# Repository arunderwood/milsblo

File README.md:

# milsblo

**milsblo** is a portmanteau of **[MILSBO](https://www.ikea.com/us/en/p/milsbo-glass-door-cabinet-anthracite-30396448/)** — IKEA's popular glass-door cabinet — and ***blow***, for the fan-control feature at the heart of the board.

> An experiment in vibe-coded circuit design by someone without much electronics experience.

## Background

Hobbyists convert MILSBO cabinets into [miniature indoor greenhouses](https://daught.me/blog/2024/ikea-milsbo-greenhouse/) using grow lights, humidifiers, and fans. Circulation fans are critical: airflow strengthens stems and prevents the mold that thrives in warm, stagnant, humid air.

**milsblo** is the electronics backbone for that setup.

## What it does

A 12V DC supply on a 5.5 × 2.1mm barrel jack powers both fans and the microcontroller from one cord. The board backpacks onto an ESP32-S3-DevKitC-1 via female pin headers.

```
12V DC supply (centre positive, 1.5A+)
    │
    ▼
Barrel jack → AO3407A → 12V rail ──→ Fan headers × 2 (always-on 12V)
                                └──→ AP63205 buck → 5V → ESP32-S3-DevKitC-1
                                                         │
                                                         ├── 25kHz PWM → Fan 1 & 2 speed control
                                                         ├── Tach input ← Fan RPM feedback
                                                         └── I2C → BME280 temp/humidity sensor
```

- **Power:** 12V barrel jack with reverse-polarity protection (AO3407A); stepped to 5V by AP63205 buck converter
- **Fan control:** 25kHz PWM on GPIO 4/5 (silent, full-range speed), tach feedback on GPIO 6/7
- **Sensor:** BME280 via JST-SH 4-pin (Qwiic/STEMMA QT compatible) on I2C GPIO 8/9
- **Firmware:** ESPHome (`firmware/milsblo.yaml`) — integrates with Home Assistant

## Project status

| Phase | Status |
|-------|--------|
| Phase 1: Component definitions | ✅ Complete |
| Phase 2: KiCad schematic | ✅ Complete |
| Phase 3: SPICE simulations | ✅ Complete |
| Phase 4: Firmware + test guide | ✅ Complete |
| Phase 5: PCB layout (KiCad) | ✅ Complete |
| Phase 6: Manufacturing export | ✅ Complete (`tools/export_fab.sh`) |

## Design

Designed in [KiCad](https://www.kicad.org/). The project lives in `elec/kicad/`, and `tools/check_design.py` checks it against the part datasheets.

**For full architecture decisions and build instructions, see [CLAUDE.md](CLAUDE.md).**

## Toolchain

```bash
python3 tools/check_design.py       # ERC, DRC, parity, connectivity, datasheet and layout rules
tools/export_fab.sh                 # Gerber zip, BOM and pick-and-place in elec/build/fab
ngspice -b simulation/power_chain.cir
esphome run firmware/milsblo.yaml
```

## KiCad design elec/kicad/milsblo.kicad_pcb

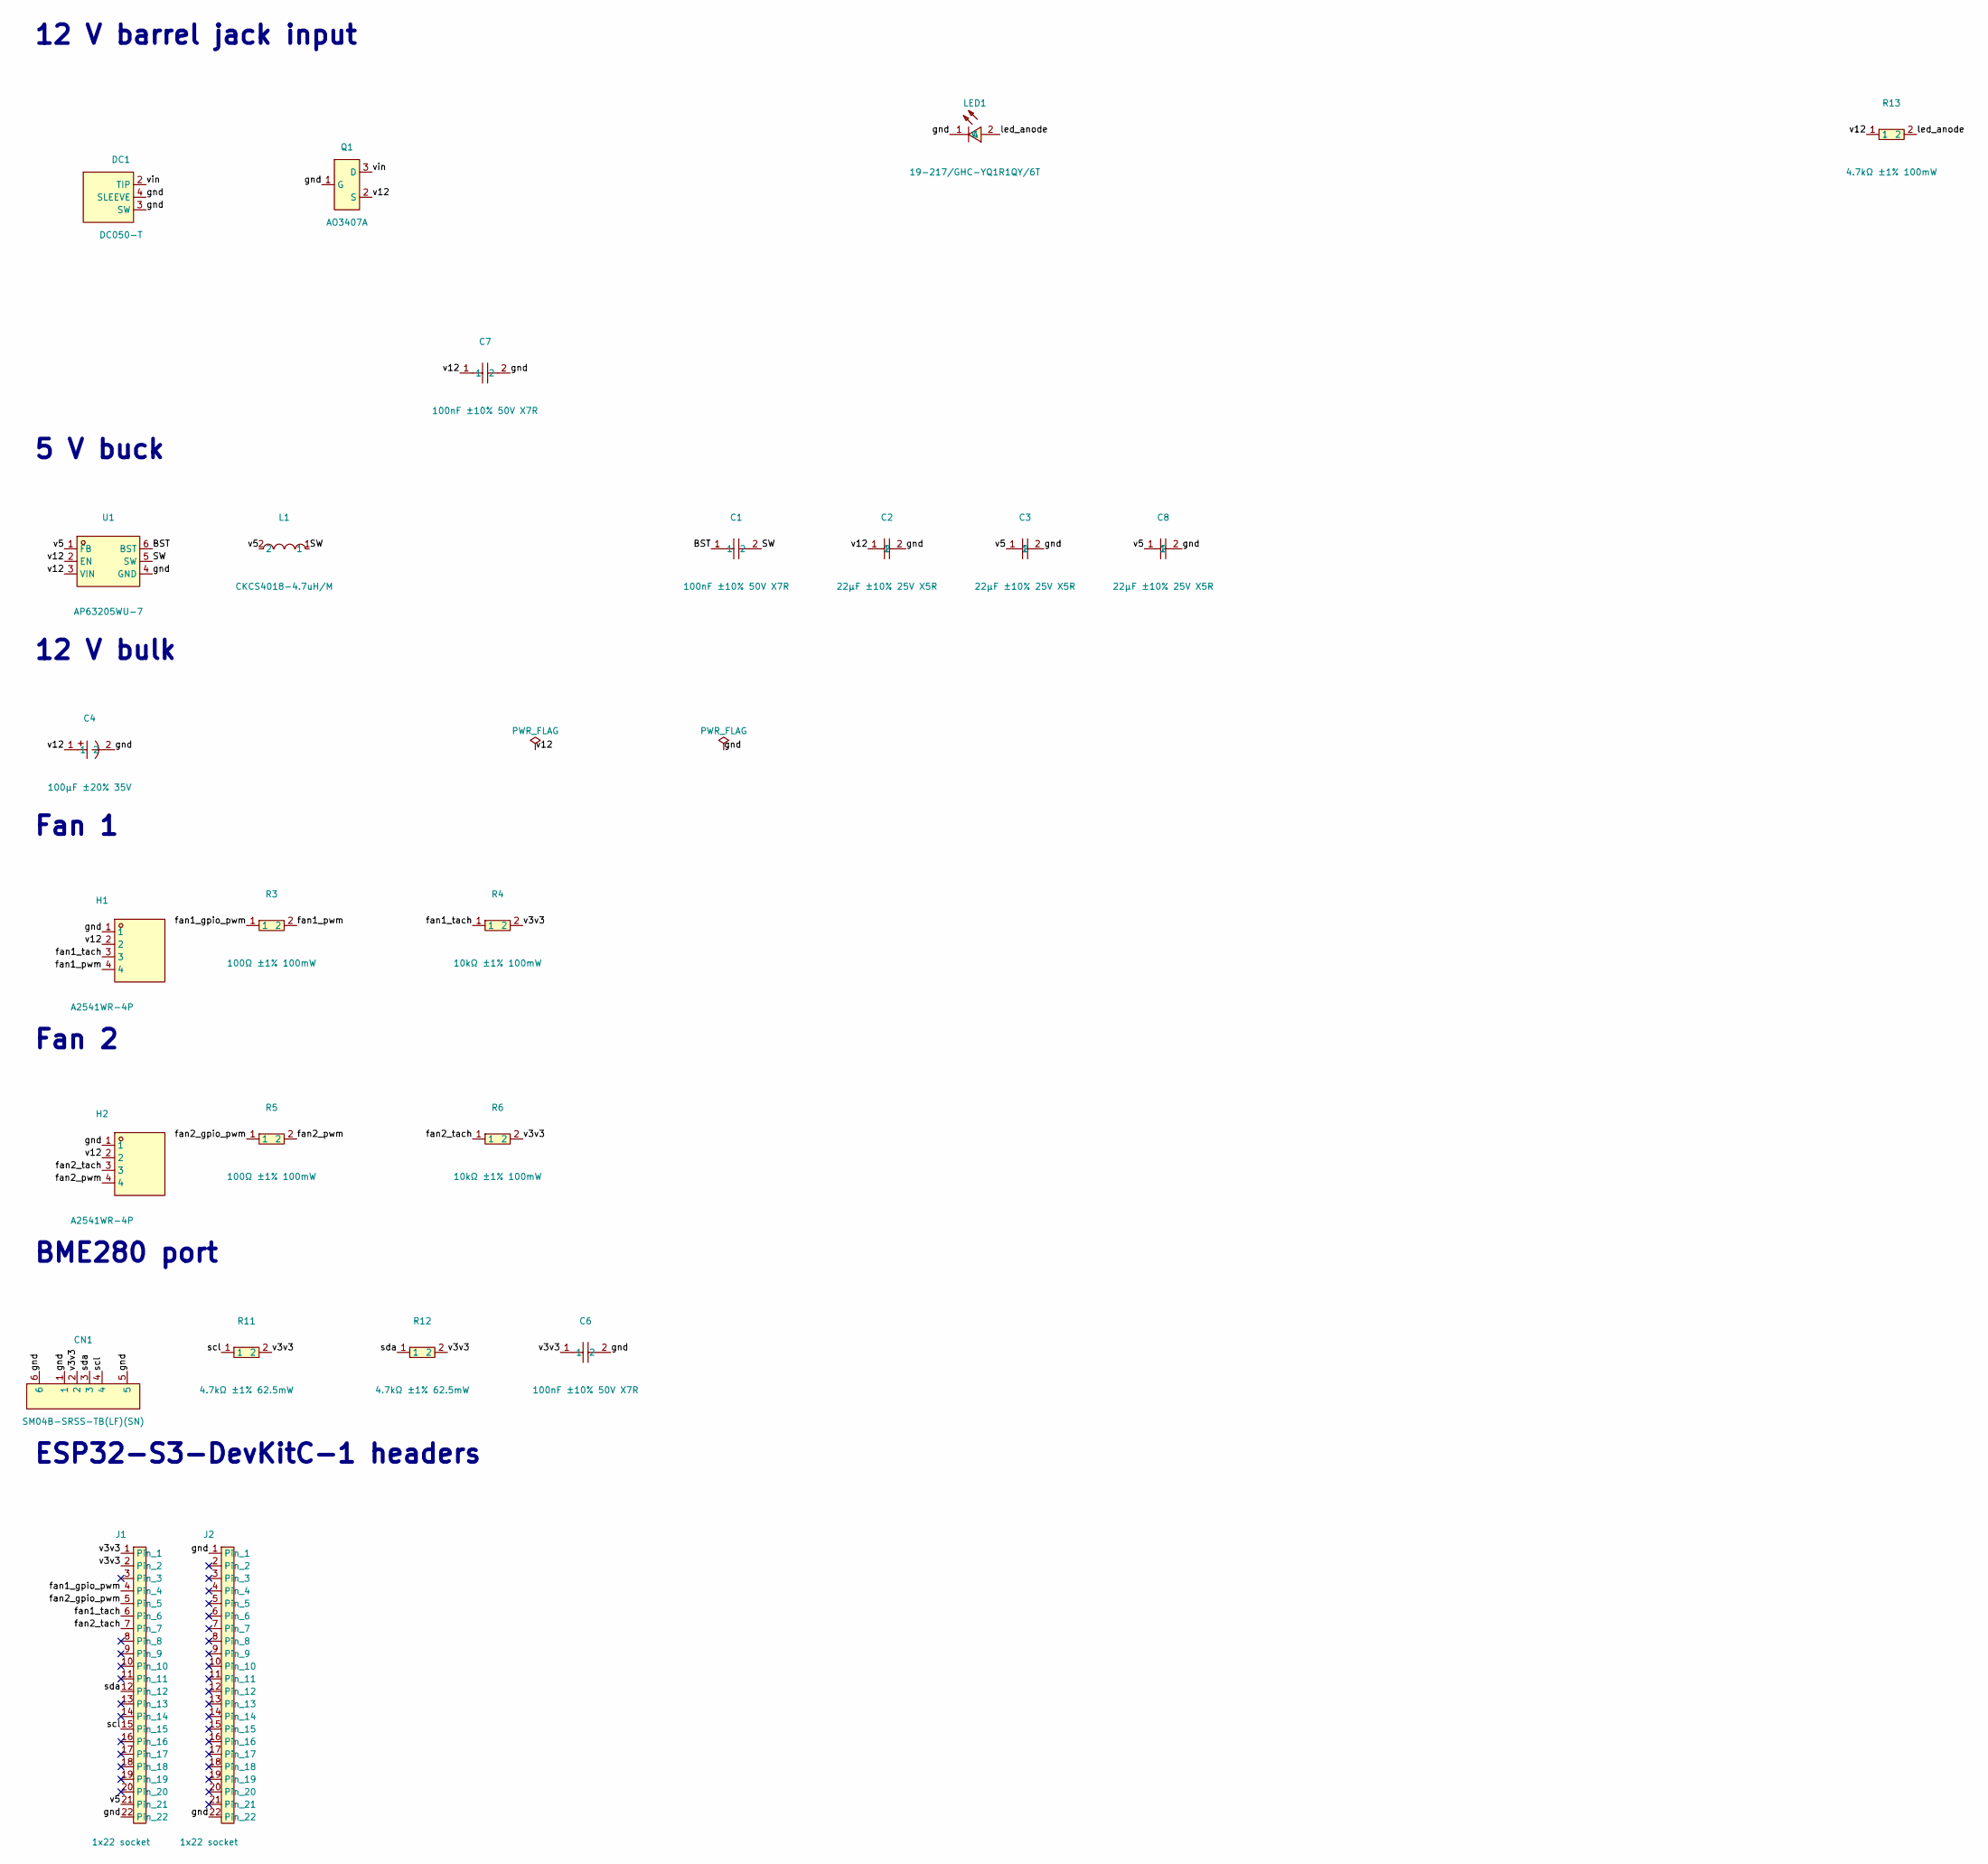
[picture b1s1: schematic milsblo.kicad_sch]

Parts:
C1, C6, C7: 100nF ±10% 50V X7R; C0603; Partnumber CC0603KRX7R9BB104; LCSC Part C14663
C2, C3, C8: 22µF ±10% 25V X5R; C1206; Partnumber CL31A226KAHNNNE; LCSC Part C12891
C4: 100µF ±20% 35V; CAP-SMD_BD6.3-L6.6-W6.6-FD; Partnumber RVT100UF35V167RV0082; LCSC Part C5138965
CN1: SM04B-SRSS-TB(LF)(SN); CONN-SMD_4P-P1.00_SM04B-SRSS-TB-LF-SN; Partnumber SM04B-SRSS-TB(LF)(SN); LCSC Part C160404
DC1: DC050-T; DC-SMD_DC050-T; Partnumber DC050-T; LCSC Part C431534
H1, H2: A2541WR-4P; HDR-TH_4P-P2.54-H-M-W10.3; Partnumber A2541WR-4P; LCSC Part C225490
J1, J2: 1x22 socket; PinSocket_1x22_P2.54mm_Vertical; Partnumber HC-PM254-8.5H-1x22PZ; LCSC Part C41376161
L1: CKCS4018-4.7uH/M; IND-SMD_L4.0-W4.0_SWPA4018S; Partnumber CKCS4018-4.7uH/M; LCSC Part C354574
LED1: 19-217/GHC-YQ1R1QY/6T; LED0603-RD; Partnumber 19-217/GHC-YQ1R1QY/6T; LCSC Part C2986032
Q1: AO3407A; SOT-23-3_L2.9-W1.6-P1.90-LS2.8-BR; Partnumber AO3407A; LCSC Part C15155
R3, R5: 100Ω ±1% 100mW; R0603; Partnumber 0603WAF1000T5E; LCSC Part C22775
R4, R6: 10kΩ ±1% 100mW; R0603; Partnumber 0603WAF1002T5E; LCSC Part C25804
R11, R12: 4.7kΩ ±1% 62.5mW; R0402; Partnumber 0402WGF4701TCE; LCSC Part C25900
R13: 4.7kΩ ±1% 100mW; R0603; Partnumber 0603WAF4701T5E; LCSC Part C23162
U1: AP63205WU-7; TSOT-23-6_L2.9-W1.6-P0.95-LS2.8-BL; Partnumber AP63205WU-7; LCSC Part C2071056

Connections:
/BST: C1.1, U1.6 (BST)
/SW: C1.2, L1.1, U1.5 (SW)
/fan1_gpio_pwm: J1.4, R3.1
/fan1_pwm: H1.4, R3.2
/fan1_tach: H1.3, J1.6, R4.1
/fan2_gpio_pwm: J1.5, R5.1
/fan2_pwm: H2.4, R5.2
/fan2_tach: H2.3, J1.7, R6.1
/gnd: C2.2, C3.2, C4.2, C6.2, C7.2, C8.2, CN1.1, CN1.5, CN1.6, DC1.3 (SW), DC1.4 (SLEEVE), H1.1, H2.1, J1.22, J2.1, J2.22, LED1.1 (C), Q1.1 (G), U1.4 (GND)
/led_anode: LED1.2 (A), R13.2
/scl: CN1.4, J1.15, R11.1
/sda: CN1.3, J1.12, R12.1
/v3v3: C6.1, CN1.2, J1.1, J1.2, R4.2, R6.2, R11.2, R12.2
/v5: C3.1, C8.1, J1.21, L1.2, U1.1 (FB)
/v12: C2.1, C4.1, C7.1, H1.2, H2.2, Q1.2 (S), R13.1, U1.2 (EN), U1.3 (VIN)
/vin: DC1.2 (TIP), Q1.3 (D)

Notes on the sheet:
12 V bulk
12 V barrel jack input
5 V buck
BME280 port
Fan 1
ESP32-S3-DevKitC-1 headers
Fan 2

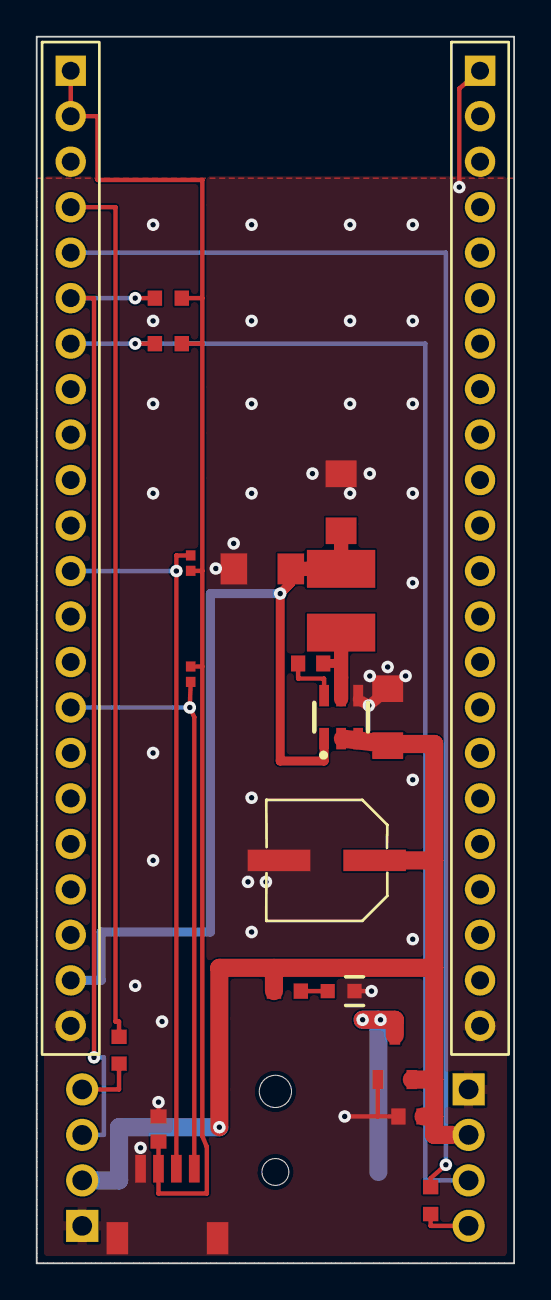
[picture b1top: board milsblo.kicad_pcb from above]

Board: 2 copper layers, 26.7 x 68.5 mm, 24 parts (1 on the bottom side), 16 nets.

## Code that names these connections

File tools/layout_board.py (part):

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    path("/gnd", F, SIG_W, (19.05, 58.24), (19.05, 60.3)),
    path("/gnd", F, SIG_W, (20.2, 60.3), (17.2, 60.3)),
    # 3.3 V from the top of J1 to the pullups and the sensor connector.
    path("/v3v3", F, SIG_W, (J1_X, pin_y(1)), (J1_X, pin_y(2))),
    path("/v3v3", F, SIG_W, (J1_X, pin_y(2)), (3.4, pin_y(2)), (3.4, 8.0), (9.25, 8.0), (9.25, 61.4), (9.5, 62.0), (9.5, 64.6), (6.8, 64.6), (6.8, 63.5)),
    path("/v3v3", F, SIG_W, (9.25, pin_y(6)), (8.1, pin_y(6))),
    path("/v3v3", F, SIG_W, (9.25, pin_y(7)), (8.1, pin_y(7))),
    path("/v3v3", F, SIG_W, (9.25, 29.83), (8.6, 29.83)),
    path("/v3v3", F, SIG_W, (9.25, 35.17), (8.6, 35.17)),
    path("/v3v3", F, SIG_W, (6.8, 61.7), (6.8, 62.8)),
    path("/gnd", F, SIG_W, (6.8, 60.3), (6.8, 59.5)),
    # Fan 1
    path("/fan1_gpio_pwm", F, SIG_W, (J1_X, pin_y(4)), (4.4, pin_y(4)), (4.4, 55.0), (4.6, 55.0), (4.6, 55.85)),
    path("/fan1_pwm", F, SIG_W, (4.6, 57.35), (4.6, 58.79), (3.44, 58.79)),
    path("/fan1_tach", F, SIG_W, (J1_X, pin_y(6)), (3.2, pin_y(6)), (3.2, 57.0)),
    path("/fan1_tach", B, SIG_W, (3.2, 57.0), (3.75, 57.0), (3.75, 61.33), (3.2, 61.33)),
    path("/fan1_tach", B, SIG_W, (J1_X, pin_y(6)), (5.5, pin_y(6))),
    path("/fan1_tach", F, SIG_W, (5.5, pin_y(6)), (6.6, pin_y(6))),
    # Fan 2 crosses on the bottom layer, under the fan 1 and I2C verticals.
    path("/fan2_gpio_pwm", B, SIG_W, (J1_X, pin_y(5)), (22.85, pin_y(5)), (22.85, 63.0)),
    path("/fan2_gpio_pwm", F, SIG_W, (22.85, 63.0), (22.0, 63.75), (22.0, 64.25)),
    path("/fan2_pwm", F, SIG_W, (22.0, 65.75), (22.0, 66.41), (23.22, 66.41)),
    path("/fan2_tach", B, SIG_W, (J1_X, pin_y(7)), (21.7, pin_y(7)), (21.7, 63.87), (23.22, 63.87)),
    path("/fan2_tach", F, SIG_W, (5.5, pin_y(7)), (6.6, pin_y(7))),
    # I2C
    path("/sda", B, SIG_W, (J1_X, pin_y(12)), (7.8, pin_y(12))),
    path("/sda", F, SIG_W, (7.8, pin_y(12)), (7.8, 62.45)),
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    ("/vin", 18.2, 54.9),
    ("/vin", 19.2, 54.9),
    ("/fan1_tach", 3.2, 57.0),
    ("/fan1_tach", 5.5, pin_y(6)),
    ("/fan2_tach", 5.5, pin_y(7)),
    ("/fan2_gpio_pwm", 22.85, 63.0),
    ("/sda", 7.8, pin_y(12)),
    ("/scl", 8.55, pin_y(15)),
    # Ground: regulator return, capacitor returns and pad tie-downs.
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
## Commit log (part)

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2026-02-17 Fix CLAUDE.md hardware design errors and add missing caveats
    Correct fan header pinout for low-side N-MOSFET switching topology,
    add tach signal validity caveat, fix DevKit board dimensions, pin
    Atopile to stable v0.12.x, add AP63205 thermal via requirement,
    USB-C connector verification note, BME280 self-heating offset,
    CH224K PD version info, and 3.3V current budget clarification.
2026-02-17 Initialize uv project and Atopile structure
    - Set up uv project with Python 3.13 (atopile 0.12.5 requirement)
    - Add atopile>=0.12,<0.13 dependency (pinned to stable release)
    - Create elec/ directory with modular src/ structure:
    - src/milsblo.ato (top-level board module)
    - src/power/ (usb_pd.ato, buck_5v.ato)
    - src/fan/ (fan_driver.ato)
2026-02-17 Replace PlatformIO firmware with ESPHome configuration
    Change Phase 7 from writing C++ firmware to crafting ESPHome YAML:
    - Complete milsblo.yaml with fan control, BME280 sensor, and tach reading
    - LEDC PWM at 25kHz on GPIO 4/5 for silent fan operation
    - Pulse counter for tach on GPIO 6/7 with RPM calculation
    - BME280 I2C with -1°C offset for self-heating compensation
    - Native Home Assistant integration via API
2026-02-18 Update CLAUDE.md for 4-pin PWM fan topology
    Remove AO3400A MOSFET and SS14 flyback diode (4-pin fans have internal
    controllers). Update fan headers from 3-pin to 4-pin throughout. Fix
    AP63205WU-7 LCSC part number (C2890835 → C2071056). Update fan driver
    description, breadboard BOM, Phase 3 SPICE items, layout priorities,
    and tach accuracy note. Add warning that 3-pin fans will run at full speed.
2026-02-18 Phase 1: Create component definitions from LCSC parts
    Add generated .ato component files for all Phase 1 parts:
    - CH224K USB-C PD sink (C970725)
    - AP63205WU-7 12V→5V buck converter (C2071056)
    - SHOU HAN TYPE-C 16PIN 2MD(073) USB-C connector (C2765186)
    - SM04B-SRSS-TB JST-SH 4-pin Qwiic connector, right-angle (C160404)
    - A2541WR-4P 4-pin 2.54mm fan header, right-angle ×2 (C225490)
2026-02-18 Phase 2: Schematic entry — full circuit connections in Atopile
    - Add subsystem modules: usb_pd.ato, buck_5v.ato, fan_driver.ato, sensor_port.ato
    - Wire top-level milsblo.ato composing all subsystems with correct net names
    - Add named signal aliases (p1–p6) to CJT and JST connector parts to work
    around bare-pin access limitation in atopile v0.12.5
    - Auto-picked passive parts committed (resistors, caps, inductor) from ato build
    - CH224K VDD zener clamp deferred to Phase 5 (needs interactive ato create part)
2026-02-18 Phase 3: SPICE simulations for power chain and fan PWM driver
    - simulation/power_chain.cir: behavioral AP63205 buck model validating
    5.075V output at 500mA (incl. DCR drop), 12.3mV ripple pk-pk, and
    load-step transient response
    - simulation/fan_driver.cir: ESP32 GPIO → 100Ω → fan pin 4 RC path;
    confirms 3.3V logic HIGH and 3.3µs rise time (well within 25kHz spec)
    - simulation/README.md: run instructions and full results table
2026-02-20 Phase 4: Breadboard prototype — firmware, test guide, Zener fix
    Add BZT52C5V1 (LCSC C173407) 5.1V Zener clamp to usb_pd.ato to protect
    CH224K VDD pin from 12V VBUS after PD negotiation (was unprotected; IC
    would be destroyed without it). Add ESPHome firmware config and
    breadboard test guide with 6-stage test sequence.
    - elec/src/power/usb_pd.ato: add z_vdd Zener clamp (C→VDD, A→GND)
    - elec/src/parts/MDD_Microdiode_Electronics_BZT52C5V1/: new Zener part
2026-02-20 Phase 4 review: fix simulation Fsw, flag wrong inductor, housekeeping
    - simulation/power_chain.cir: correct Fsw 580kHz → 1.5MHz (AP63205WU-7
    datasheet); recalculate ΔIL (1.07A → 0.416A pk-pk), ripple (13.7mV →
    2.83mV), update DCR to 90mΩ for replacement inductor
    - simulation/README.md: update all derived values; document inductor
    replacement requirement with confirmed part
    - elec/src/power/buck_5v.ato: flag auto-selected FH CMP201209UD4R7KT
2026-02-20 fix(buck): replace auto-selected inductor with explicit CENKER CKCS4018-4.7uH/M
    The generic Inductor constraint caused Atopile to select FH CMP201209UD4R7KT
    (C395016), a multilayer chip inductor rated at only 350mA — it would saturate
    at 2× peak current (708mA). Replace with explicit CENKER CKCS4018-4.7uH/M
    (C354574): Isat=1.7A, DCR=90mΩ, SMD 4018 package.
2026-02-20 feat(headers): add ESP32-S3-DevKitC-1 female header interface
    Hand-crafted 1×22 2.54mm KiCad footprint/symbol (no LCSC number needed —
    snap from BOOMELE C9811 1×40P). ESP32Headers module wires all 44 pins:
    GND, 3V3, 5V, GPIO4-10 connected; NC pins left unconnected. milsblo.ato
    updated to use ESP32Headers; v3v3 now properly sourced through header.
    ato build passes with correct footprint in netlist.
2026-02-20 fix(review): pre-layout design review — voltage ratings, GPIO10, PG LED
    Bugs fixed:
    - Add max_voltage = 25V to 10000V on c_bulk (milsblo.ato) and c_in (buck_5v.ato)
    to prevent solver picking low-voltage parts (e.g. 6.3V AVX TAJB) on the 12V rail.
    Solver now picks KNSCHA RVT100UF35V167RV0082 (100µF 35V) for c_bulk.
    - Disconnect GPIO10 from CH224K PG net: PG may be push-pull to VDD (5.1V), which
    exceeds ESP32 GPIO absolute maximum of 3.6V.
2026-02-20 docs(readme): flesh out project story — name origin, greenhouse context, USB-PD rationale
2026-02-20 ci: move workflows to repo root, add KiCad PCB SVG artifact
    - Relocate .github/workflows/ from elec/ to repo root (GitHub only
    recognises workflows at the repository root)
    - Add descriptive names to ato sync and ato build steps
    - Install KiCad 8 from PPA and export PCB layout as SVG after build
    - SVG lands in elec/build/ and is captured by the existing artifact upload
    - continue-on-error on SVG export so CI passes before Phase 5 layout
2026-02-20 ci: fix setup-atopile working-directory to find ato.yaml in elec/
2026-02-20 ci: pin Python 3.11 for atopile 0.12.x compatibility
2026-02-20 ci: use Python 3.13 to match local dev environment
2026-02-20 ci: read Python version from .python-version file
2026-02-24 fix(ci): split deprecated multi-imports, drop KiCad PPA
    - Split `import Resistor, Capacitor` into separate statements in all
    three .ato files — the combined form causes `p1`/`p2` to be
    unresolvable in the CI version of atopile 0.12.x
    - Remove `ppa:kicad/kicad-8-releases` (doesn't exist on Ubuntu 24.04);
    Ubuntu 24.04 ships KiCad 8 in the standard repos
2026-02-24 ci: fail fast — remove continue-on-error from build step
2026-02-24 ci: install via uv sync from lock file
    Replaces setup-atopile (which ignored requires-atopile and installed
    latest) with setup-uv + uv sync, which installs the exact versions from
    uv.lock. Drops actions/setup-python since uv manages Python via
    pyproject.toml requires-python.
2026-02-24 ci: use kicad-9-releases PPA for format 20241229 support
2026-02-24 ci: use kicad9_auto Docker image for SVG export
    Both kicad-8-releases and kicad-9-releases PPAs are unavailable on
    Ubuntu 24.04 Noble. Drop the apt install step and run kicad-cli via
    ghcr.io/inti-cmnb/kicad9_auto — the standard PCB CI container,
    which includes KiCad 9 with full kicad-cli support.
2026-02-24 ci: embed PCB SVG preview in job summary
2026-02-24 ci: fix PCB preview — commit SVG to docs/ for raw.githubusercontent.com rendering
    GitHub sanitizes data: URIs in job summaries, so the base64 inline approach
    doesn't render. Instead, on main-branch pushes the CI bot commits the exported
    SVG to docs/pcb-layout.svg and the summary references it via raw.githubusercontent.com,
    which GitHub does render.
    Adds contents:write permission to the job.
2026-02-24 ci: update PCB layout preview [skip ci]
2026-03-12 build(deps): bump black in the uv group across 1 directory
    Bumps the uv group with 1 update in the / directory: [black](https://github.com/psf/black).
    Updates `black` from 26.1.0 to 26.3.1
    - [Release notes](https://github.com/psf/black/releases)
    - [Changelog](https://github.com/psf/black/blob/main/CHANGES.md)
    - [Commits](https://github.com/psf/black/compare/26.1.0...26.3.1)
    ---
2026-03-26 build(deps): bump requests in the uv group across 1 directory
    Bumps the uv group with 1 update in the / directory: [requests](https://github.com/psf/requests).
    Updates `requests` from 2.32.5 to 2.33.0
    - [Release notes](https://github.com/psf/requests/releases)
    - [Changelog](https://github.com/psf/requests/blob/main/HISTORY.md)
    - [Commits](https://github.com/psf/requests/compare/v2.32.5...v2.33.0)
    ---
